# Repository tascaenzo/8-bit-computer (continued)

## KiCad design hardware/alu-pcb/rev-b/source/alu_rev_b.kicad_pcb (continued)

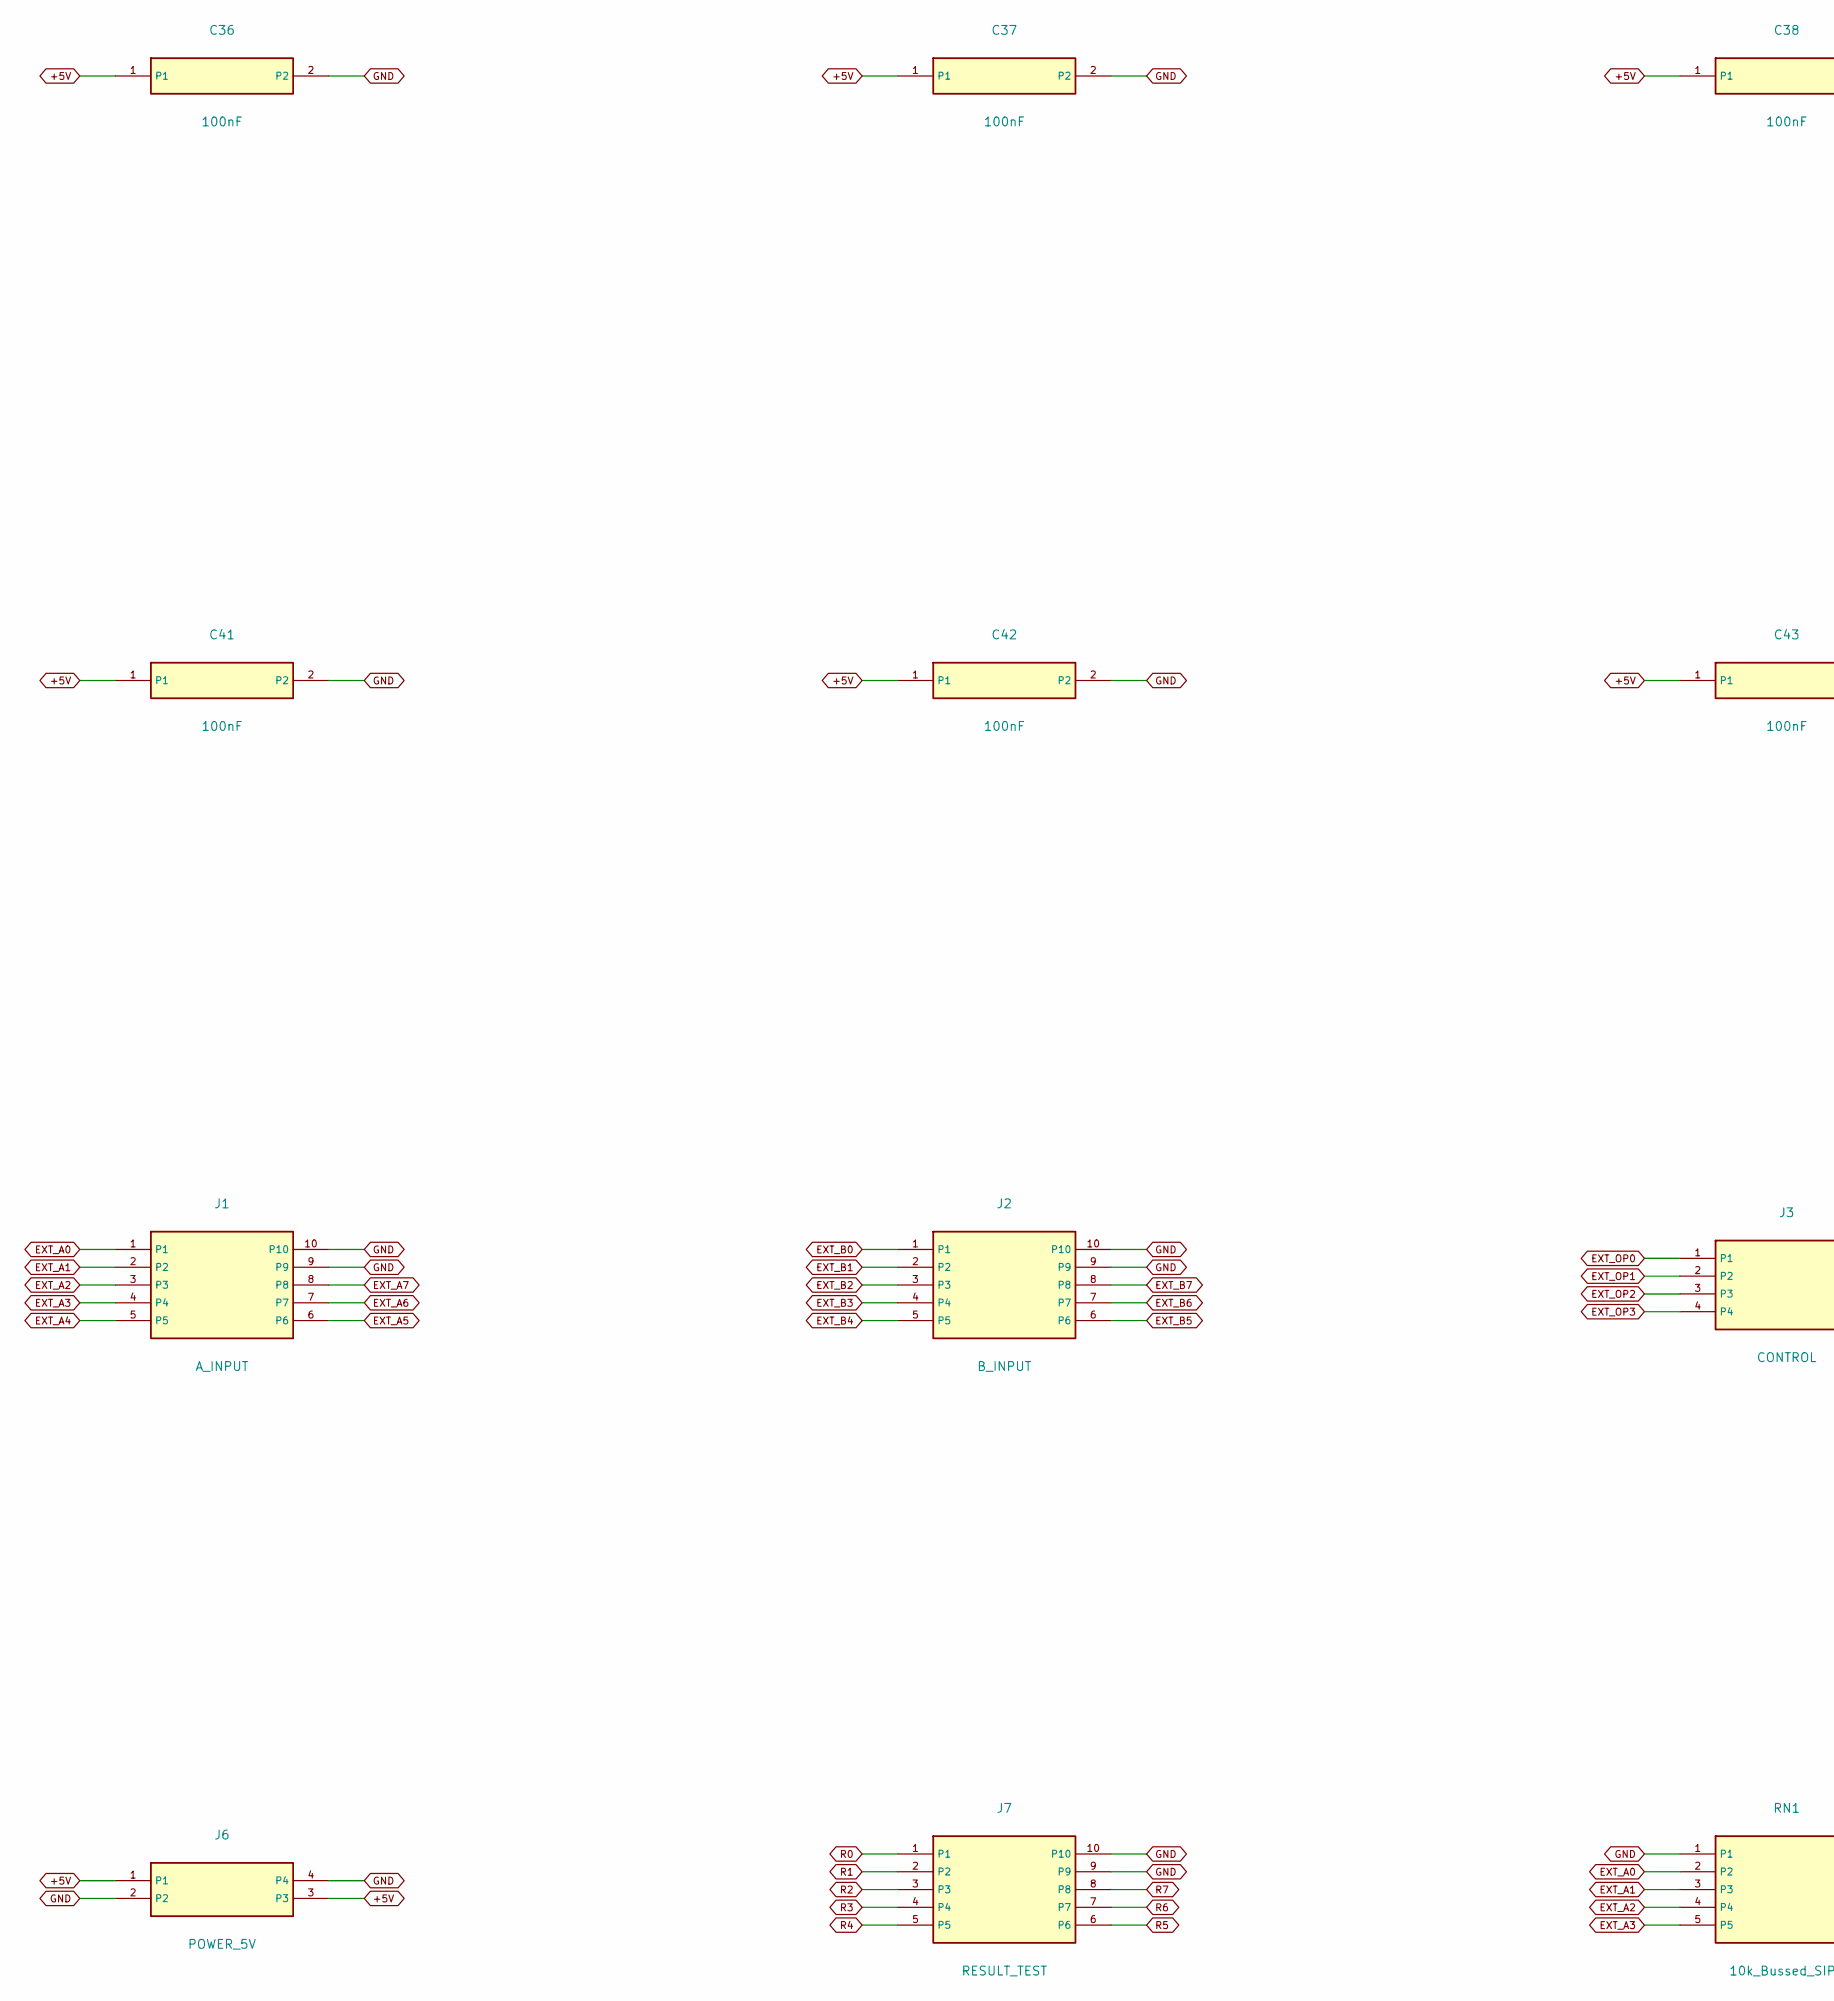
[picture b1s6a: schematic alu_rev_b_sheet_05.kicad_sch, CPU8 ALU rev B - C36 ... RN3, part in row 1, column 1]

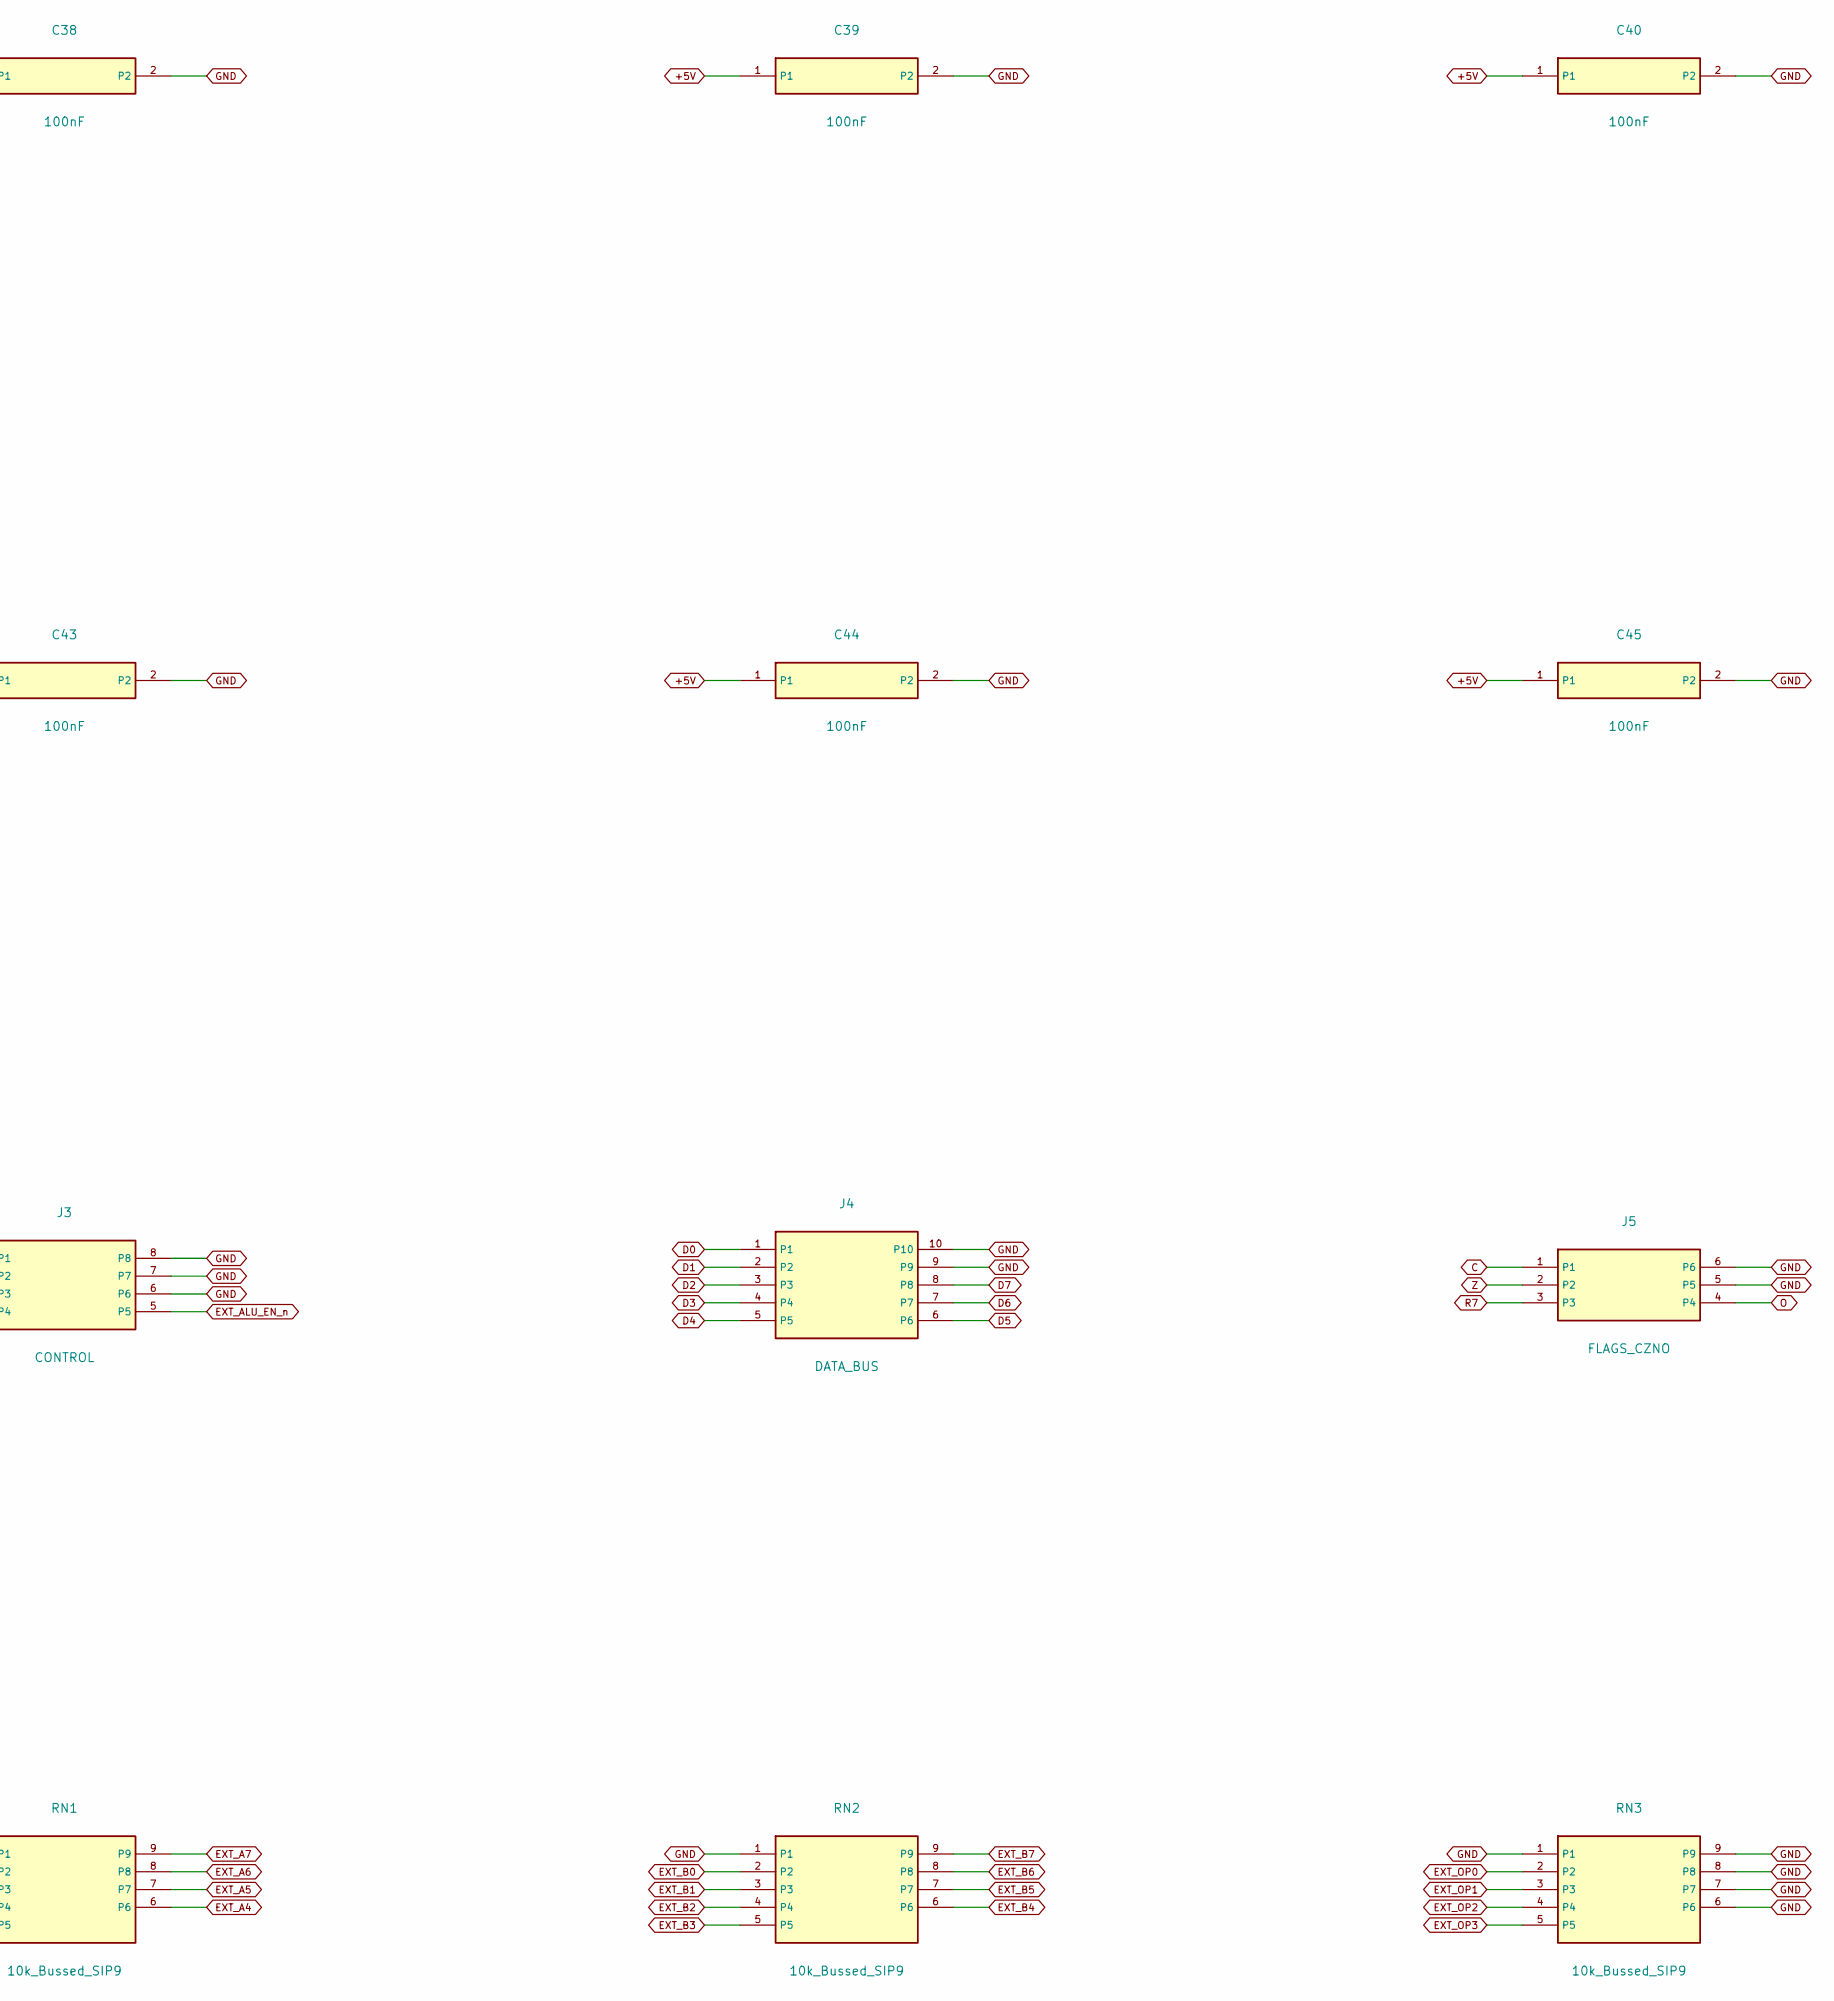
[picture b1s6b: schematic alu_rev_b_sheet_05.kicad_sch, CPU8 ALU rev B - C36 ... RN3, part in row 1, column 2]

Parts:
C36, C37, C38, C39, C40, C41, C42, C43, C44, C45: 100nF; C_Disc_P2.50mm
J1: A_INPUT; Header_2x5_P2.54mm
J2: B_INPUT; Header_2x5_P2.54mm
J3: CONTROL; Header_2x4_P2.54mm
J4: DATA_BUS; Header_2x5_P2.54mm
J5: FLAGS_CZNO; Header_2x3_P2.54mm
J6: POWER_5V; Header_2x2_P2.54mm
J7: RESULT_TEST; Header_2x5_P2.54mm
RN1, RN2, RN3: 10k_Bussed_SIP9; SIP-9_P2.54mm

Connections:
+5V: C36.1, C37.1, C38.1, C39.1, C40.1, C41.1, C42.1, C43.1, C44.1, C45.1, J6.1, J6.3; also elsewhere on the board
C: J5.1; also elsewhere on the board
D0: J4.1; also elsewhere on the board
D1: J4.2; also elsewhere on the board
D2: J4.3; also elsewhere on the board
D3: J4.4; also elsewhere on the board
D4: J4.5; also elsewhere on the board
D5: J4.6; also elsewhere on the board
D6: J4.7; also elsewhere on the board
D7: J4.8; also elsewhere on the board
EXT_A0: J1.1, RN1.2; also elsewhere on the board
EXT_A1: J1.2, RN1.3; also elsewhere on the board
EXT_A2: J1.3, RN1.4; also elsewhere on the board
EXT_A3: J1.4, RN1.5; also elsewhere on the board
EXT_A4: J1.5, RN1.6; also elsewhere on the board
EXT_A5: J1.6, RN1.7; also elsewhere on the board
EXT_A6: J1.7, RN1.8; also elsewhere on the board
EXT_A7: J1.8, RN1.9; also elsewhere on the board
EXT_ALU_EN_n: J3.5; also elsewhere on the board
EXT_B0: J2.1, RN2.2; also elsewhere on the board
EXT_B1: J2.2, RN2.3; also elsewhere on the board
EXT_B2: J2.3, RN2.4; also elsewhere on the board
EXT_B3: J2.4, RN2.5; also elsewhere on the board
EXT_B4: J2.5, RN2.6; also elsewhere on the board
EXT_B5: J2.6, RN2.7; also elsewhere on the board
EXT_B6: J2.7, RN2.8; also elsewhere on the board
EXT_B7: J2.8, RN2.9; also elsewhere on the board
EXT_OP0: J3.1, RN3.2; also elsewhere on the board
EXT_OP1: J3.2, RN3.3; also elsewhere on the board
EXT_OP2: J3.3, RN3.4; also elsewhere on the board
EXT_OP3: J3.4, RN3.5; also elsewhere on the board
GND: C36.2, C37.2, C38.2, C39.2, C40.2, C41.2, C42.2, C43.2, C44.2, C45.2, J1.9, J1.10, J2.9, J2.10, J3.6, J3.7, J3.8, J4.9, J4.10, J5.5, J5.6, J6.2, J6.4, J7.9, J7.10, RN1.1, RN2.1, RN3.1, RN3.6, RN3.7, RN3.8, RN3.9; also elsewhere on the board
O: J5.4; also elsewhere on the board
R0: J7.1; also elsewhere on the board
R1: J7.2; also elsewhere on the board
R2: J7.3; also elsewhere on the board
R3: J7.4; also elsewhere on the board
R4: J7.5; also elsewhere on the board
R5: J7.6; also elsewhere on the board
R6: J7.7; also elsewhere on the board
R7: J5.3, J7.8; also elsewhere on the board
Z: J5.2; also elsewhere on the board

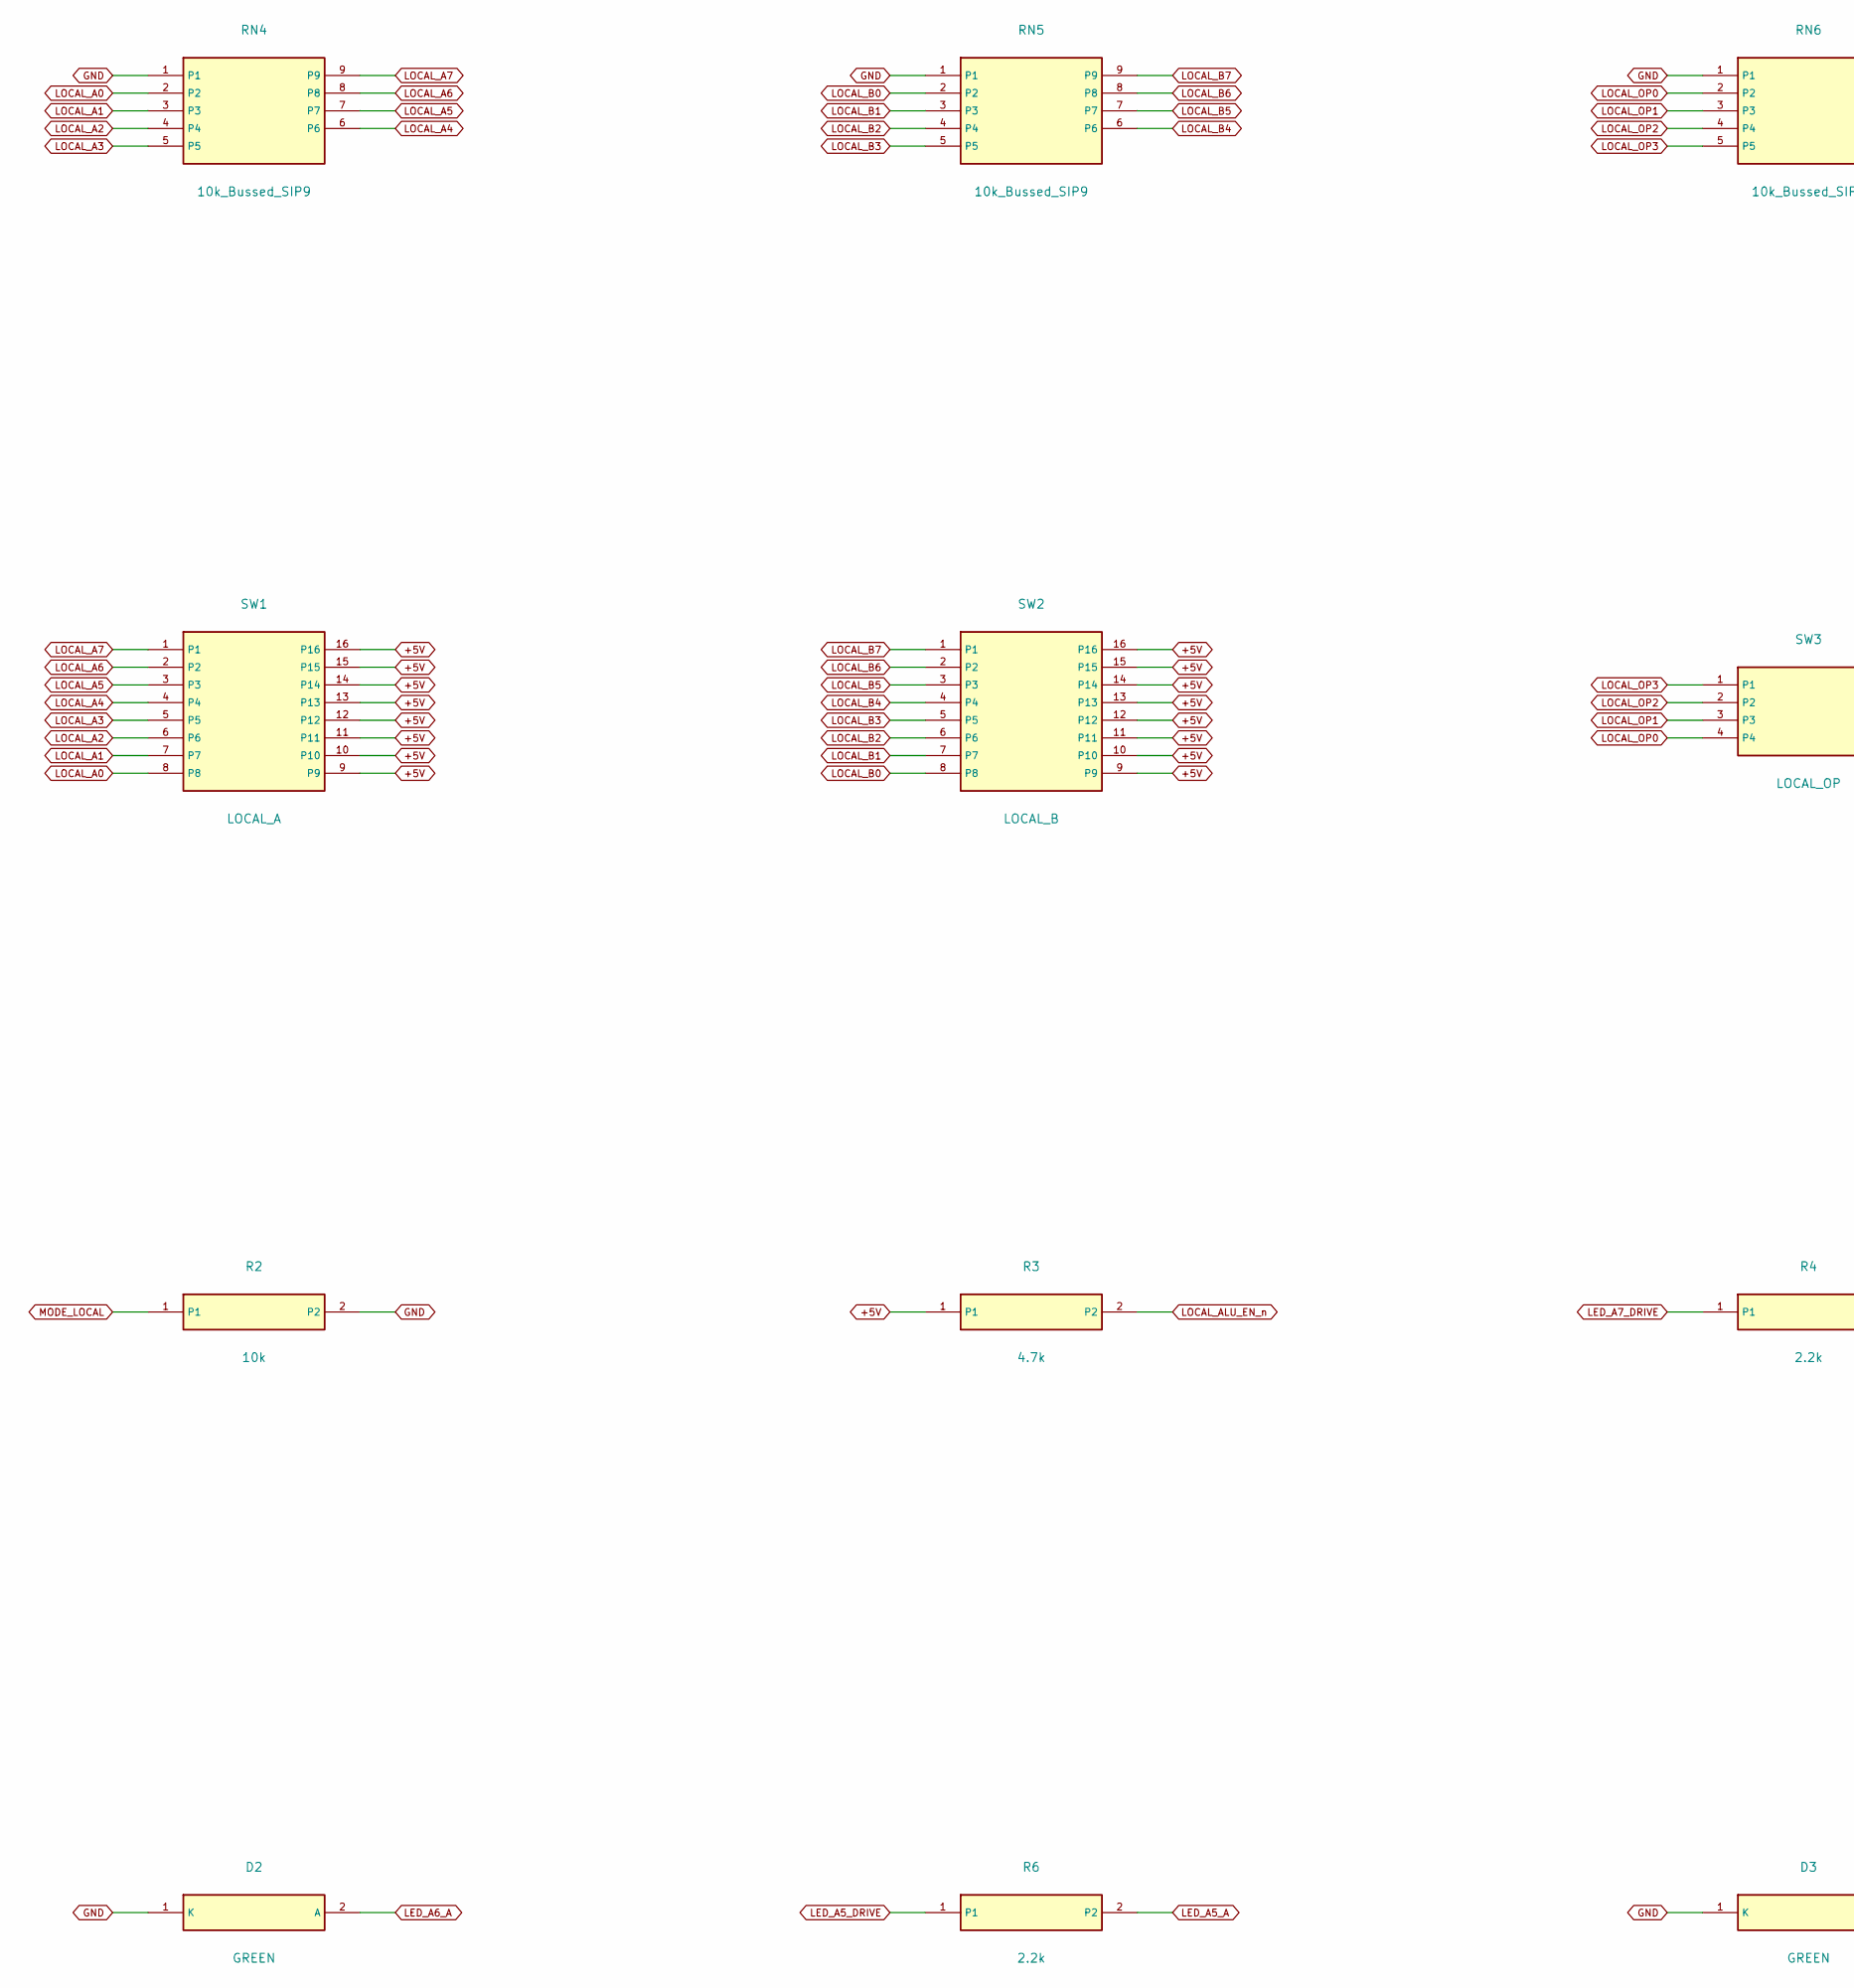
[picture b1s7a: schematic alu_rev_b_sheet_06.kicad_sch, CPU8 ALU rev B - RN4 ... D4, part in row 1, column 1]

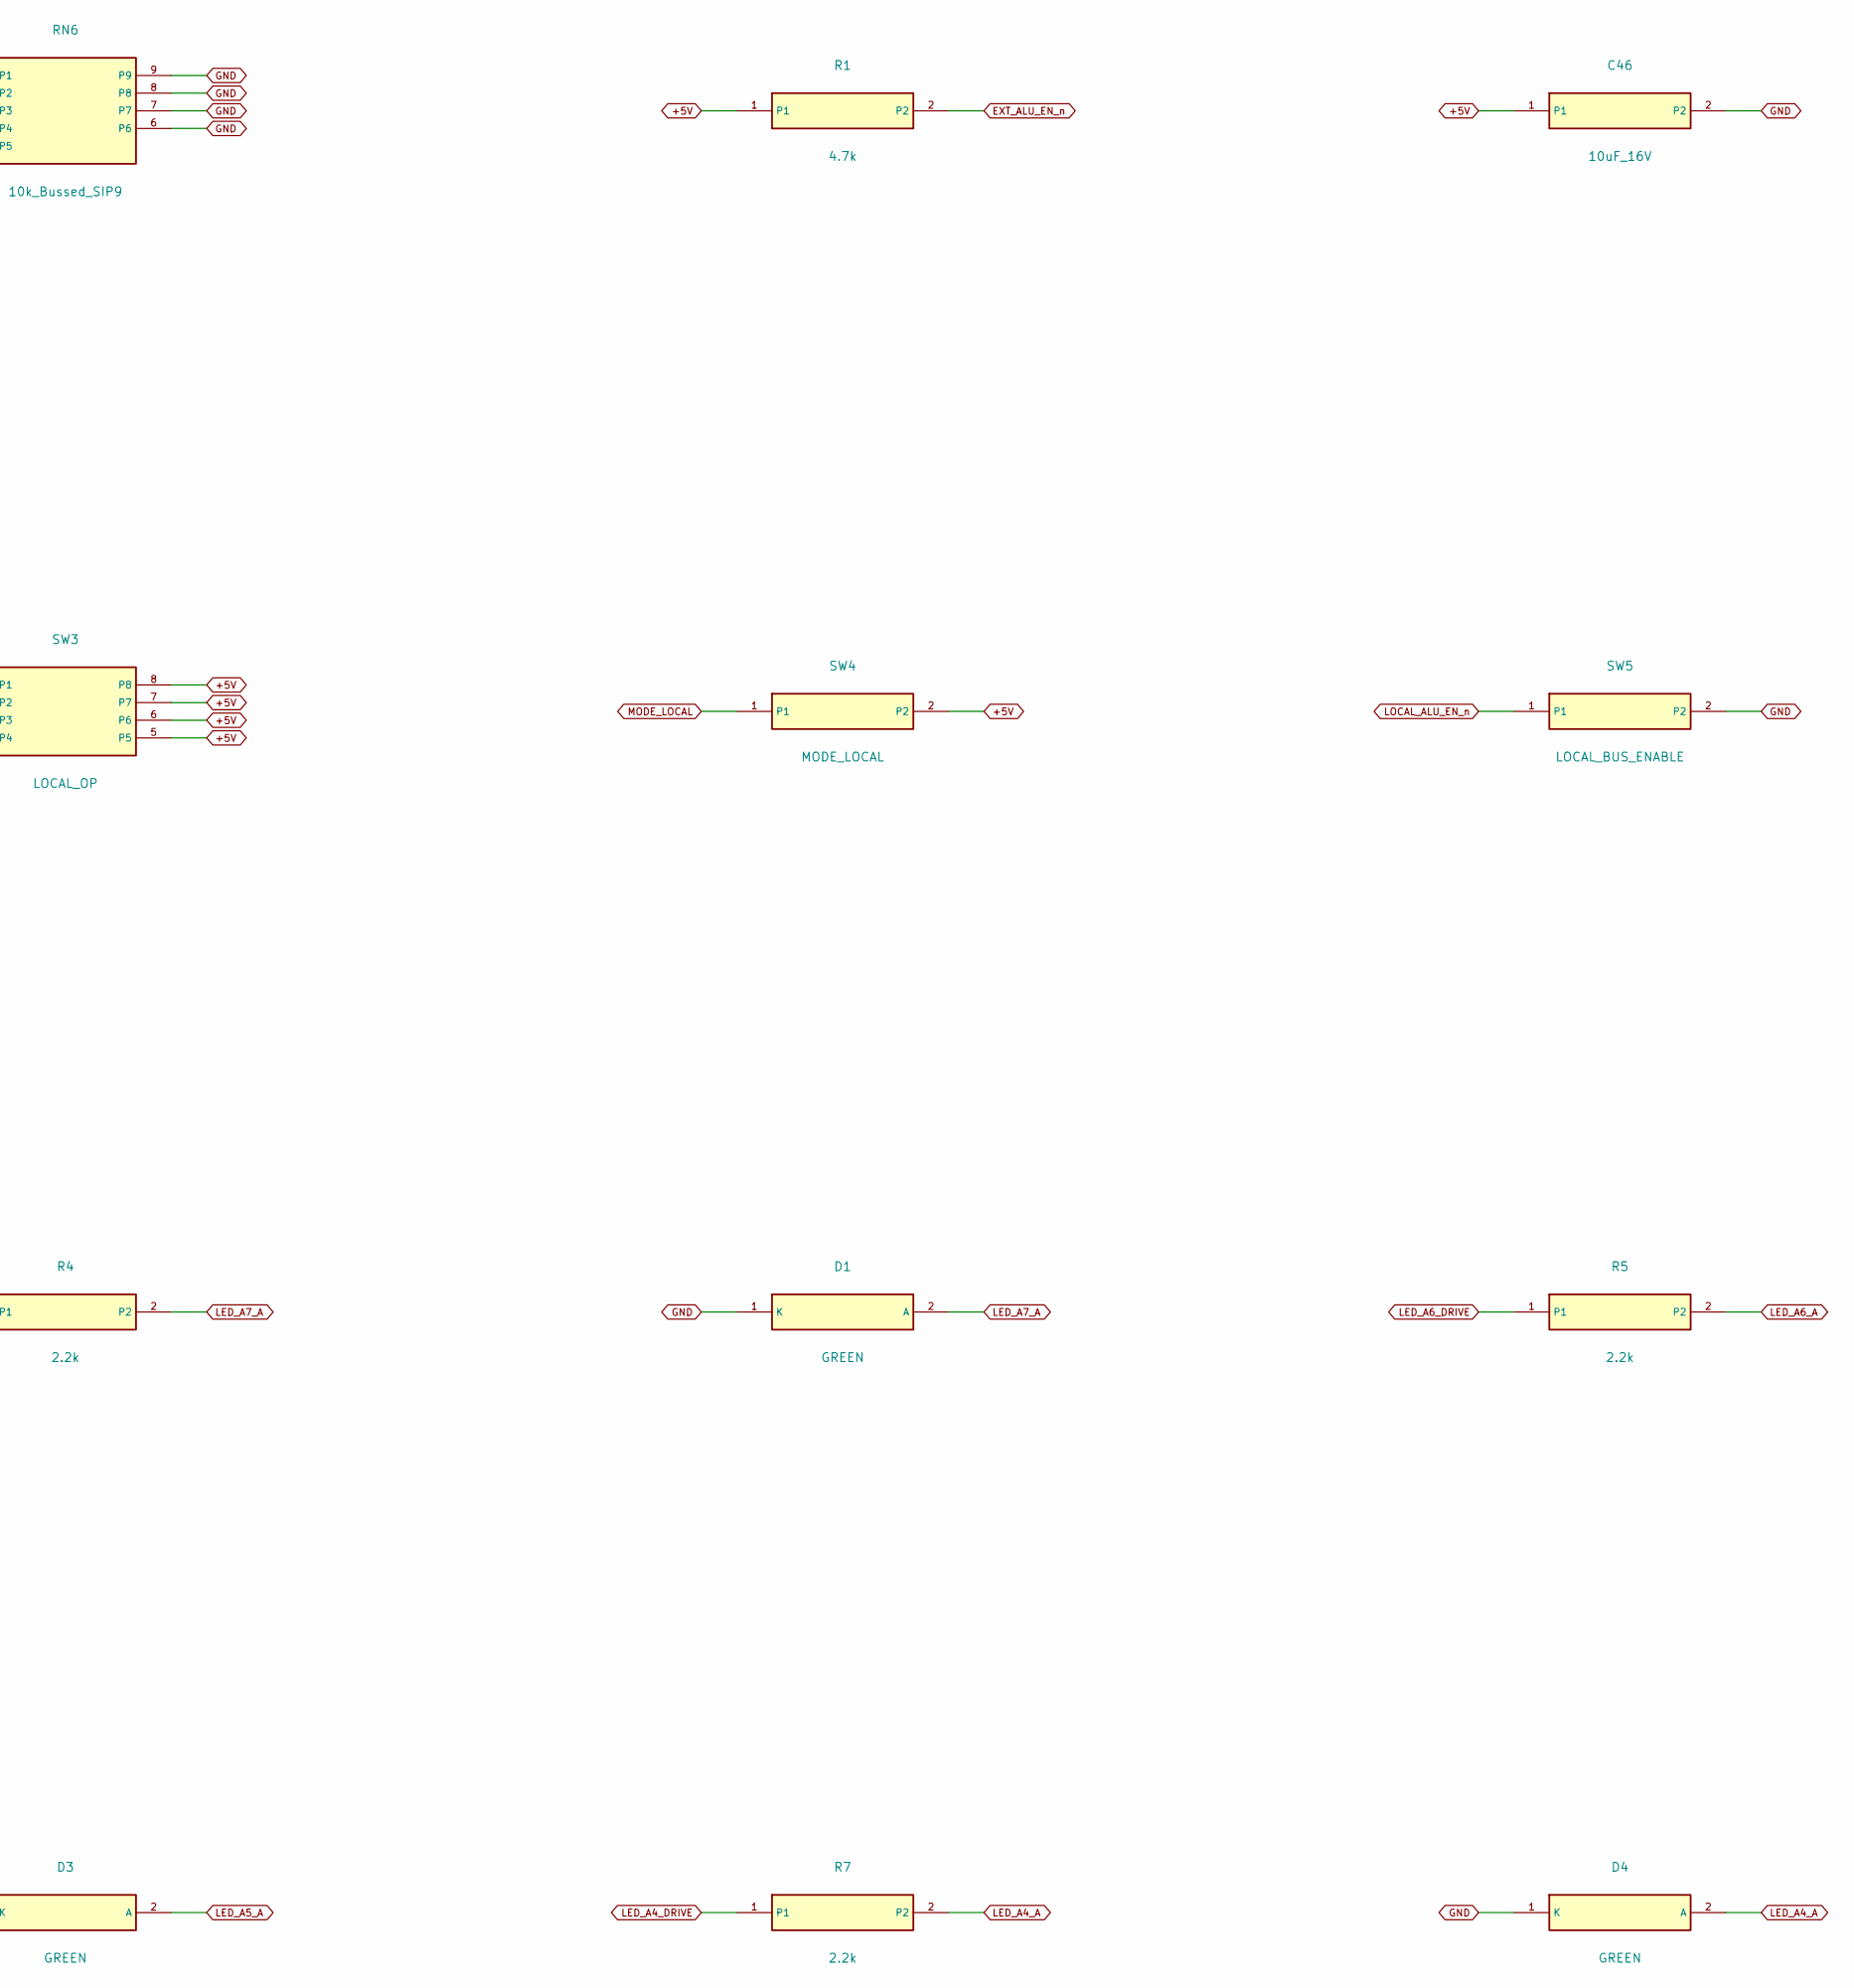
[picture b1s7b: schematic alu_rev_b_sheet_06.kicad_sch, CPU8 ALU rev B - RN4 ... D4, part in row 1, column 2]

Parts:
C46: 10uF_16V; C_Radial_P2.50mm
D1, D2, D3, D4: GREEN; LED_D3.0mm_P2.54mm
R1, R3: 4.7k; R_Axial_P7.62mm
R2: 10k; R_Axial_P7.62mm
R4, R5, R6, R7: 2.2k; R_Axial_P7.62mm
RN4, RN5, RN6: 10k_Bussed_SIP9; SIP-9_P2.54mm
SW1: LOCAL_A; SW_DIP_SPST_8_P2.54_W7.62
SW2: LOCAL_B; SW_DIP_SPST_8_P2.54_W7.62
SW3: LOCAL_OP; SW_DIP_SPST_4_P2.54_W7.62
SW4: MODE_LOCAL; SW_DIP_SPST_1_P2.54_W7.62
SW5: LOCAL_BUS_ENABLE; SW_DIP_SPST_1_P2.54_W7.62

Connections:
+5V: C46.1, R1.1, R3.1, SW1.9, SW1.10, SW1.11, SW1.12, SW1.13, SW1.14, SW1.15, SW1.16, SW2.9, SW2.10, SW2.11, SW2.12, SW2.13, SW2.14, SW2.15, SW2.16, SW3.5, SW3.6, SW3.7, SW3.8, SW4.2; also elsewhere on the board
EXT_ALU_EN_n: R1.2; also elsewhere on the board
GND: C46.2, D1.1 (K), D2.1 (K), D3.1 (K), D4.1 (K), R2.2, RN4.1, RN5.1, RN6.1, RN6.6, RN6.7, RN6.8, RN6.9, SW5.2; also elsewhere on the board
LED_A4_A: D4.2 (A), R7.2
LED_A4_DRIVE: R7.1; also elsewhere on the board
LED_A5_A: D3.2 (A), R6.2
LED_A5_DRIVE: R6.1; also elsewhere on the board
LED_A6_A: D2.2 (A), R5.2
LED_A6_DRIVE: R5.1; also elsewhere on the board
LED_A7_A: D1.2 (A), R4.2
LED_A7_DRIVE: R4.1; also elsewhere on the board
LOCAL_A0: RN4.2, SW1.8; also elsewhere on the board
LOCAL_A1: RN4.3, SW1.7; also elsewhere on the board
LOCAL_A2: RN4.4, SW1.6; also elsewhere on the board
LOCAL_A3: RN4.5, SW1.5; also elsewhere on the board
LOCAL_A4: RN4.6, SW1.4; also elsewhere on the board
LOCAL_A5: RN4.7, SW1.3; also elsewhere on the board
LOCAL_A6: RN4.8, SW1.2; also elsewhere on the board
LOCAL_A7: RN4.9, SW1.1; also elsewhere on the board
LOCAL_ALU_EN_n: R3.2, SW5.1; also elsewhere on the board
LOCAL_B0: RN5.2, SW2.8; also elsewhere on the board
LOCAL_B1: RN5.3, SW2.7; also elsewhere on the board
LOCAL_B2: RN5.4, SW2.6; also elsewhere on the board
LOCAL_B3: RN5.5, SW2.5; also elsewhere on the board
LOCAL_B4: RN5.6, SW2.4; also elsewhere on the board
LOCAL_B5: RN5.7, SW2.3; also elsewhere on the board
LOCAL_B6: RN5.8, SW2.2; also elsewhere on the board
LOCAL_B7: RN5.9, SW2.1; also elsewhere on the board
LOCAL_OP0: RN6.2, SW3.4; also elsewhere on the board
LOCAL_OP1: RN6.3, SW3.3; also elsewhere on the board
LOCAL_OP2: RN6.4, SW3.2; also elsewhere on the board
LOCAL_OP3: RN6.5, SW3.1; also elsewhere on the board
MODE_LOCAL: R2.1, SW4.1; also elsewhere on the board
